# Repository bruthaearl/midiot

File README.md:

# midiot
MIDI + IoT

Connected via the Losant IoT Platform, hacked together using libraries I don't fully comprehend.

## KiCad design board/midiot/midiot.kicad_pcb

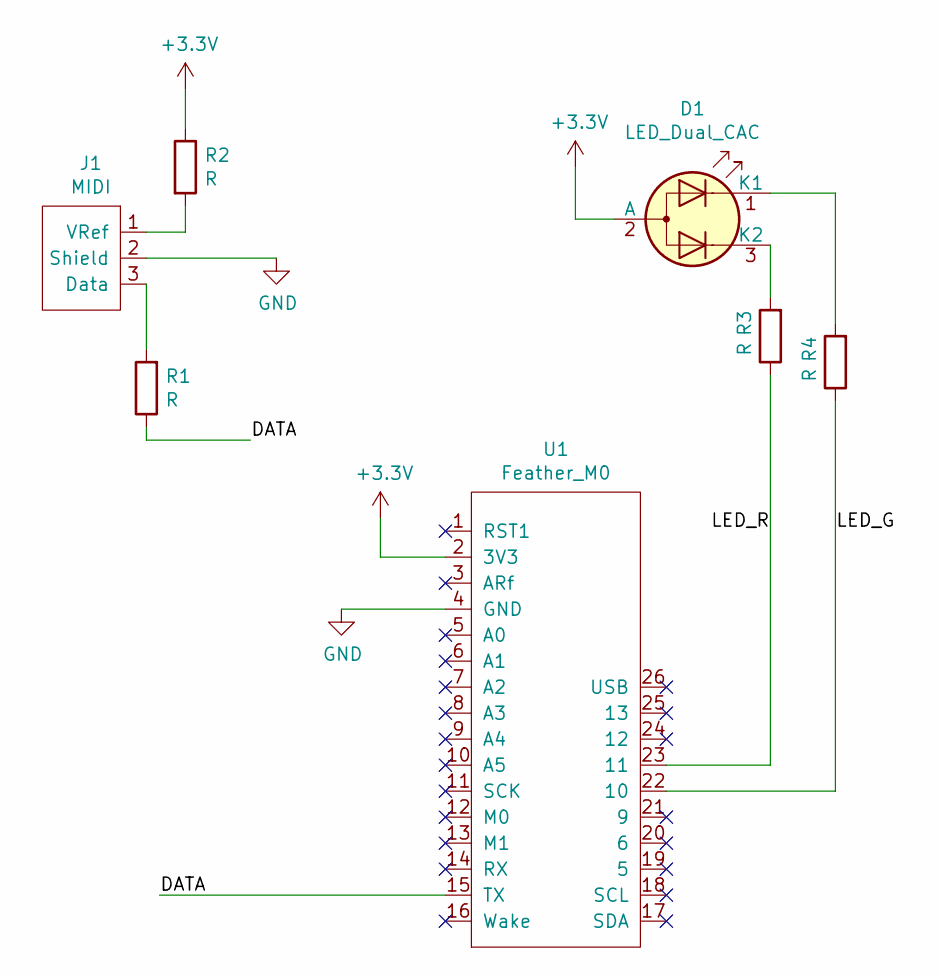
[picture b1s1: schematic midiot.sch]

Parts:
D1: LED_Dual_CAC; SolderWirePad_1x03_P3.175mm_Drill1mm
J1: MIDI; SolderWirePad_1x03_P3.175mm_Drill1mm
R1, R2, R3, R4: R; R_Axial_DIN0207_L6.3mm_D2.5mm_P10.16mm_Horizontal
U1: Feather_M0

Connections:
+3V3: D1.2 (A), R2.1, U1.2 (3V3)
/DATA: R1.1, U1.15 (TX)
/LED_G: R4.1, U1.22 (10)
/LED_R: R3.1, U1.23 (11)
GND: J1.2 (Shield), U1.4 (GND)
unnamed: D1.1 (K1), R4.2
unnamed: D1.3 (K2), R3.2
unnamed: J1.1 (VRef), R2.2
unnamed: J1.3 (Data), R1.2

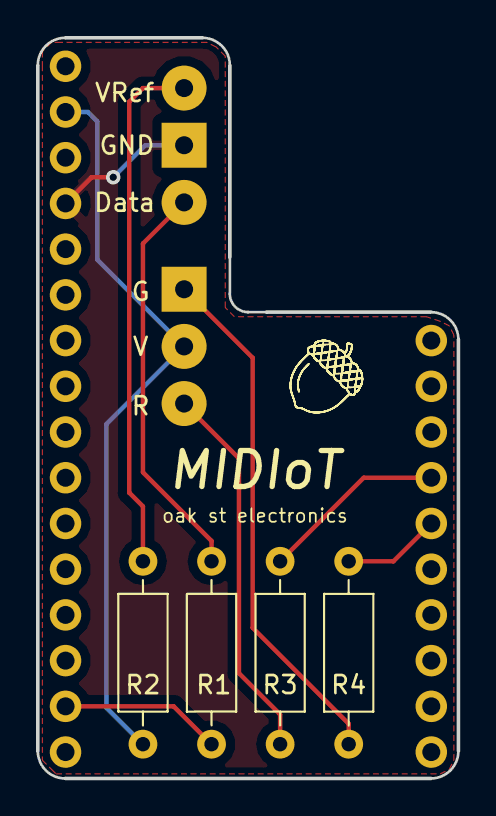
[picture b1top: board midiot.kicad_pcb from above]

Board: 2 copper layers, 23.4 x 41.1 mm, 7 parts (0 on the bottom side), 9 nets.

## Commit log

2018-10-16 git test
2019-01-21 losant connectivity
2019-02-02 mcu code done
2019-02-02 art update
2019-02-14 i think i'm done
2019-02-14 gitignore fix
2019-02-14 readme update
